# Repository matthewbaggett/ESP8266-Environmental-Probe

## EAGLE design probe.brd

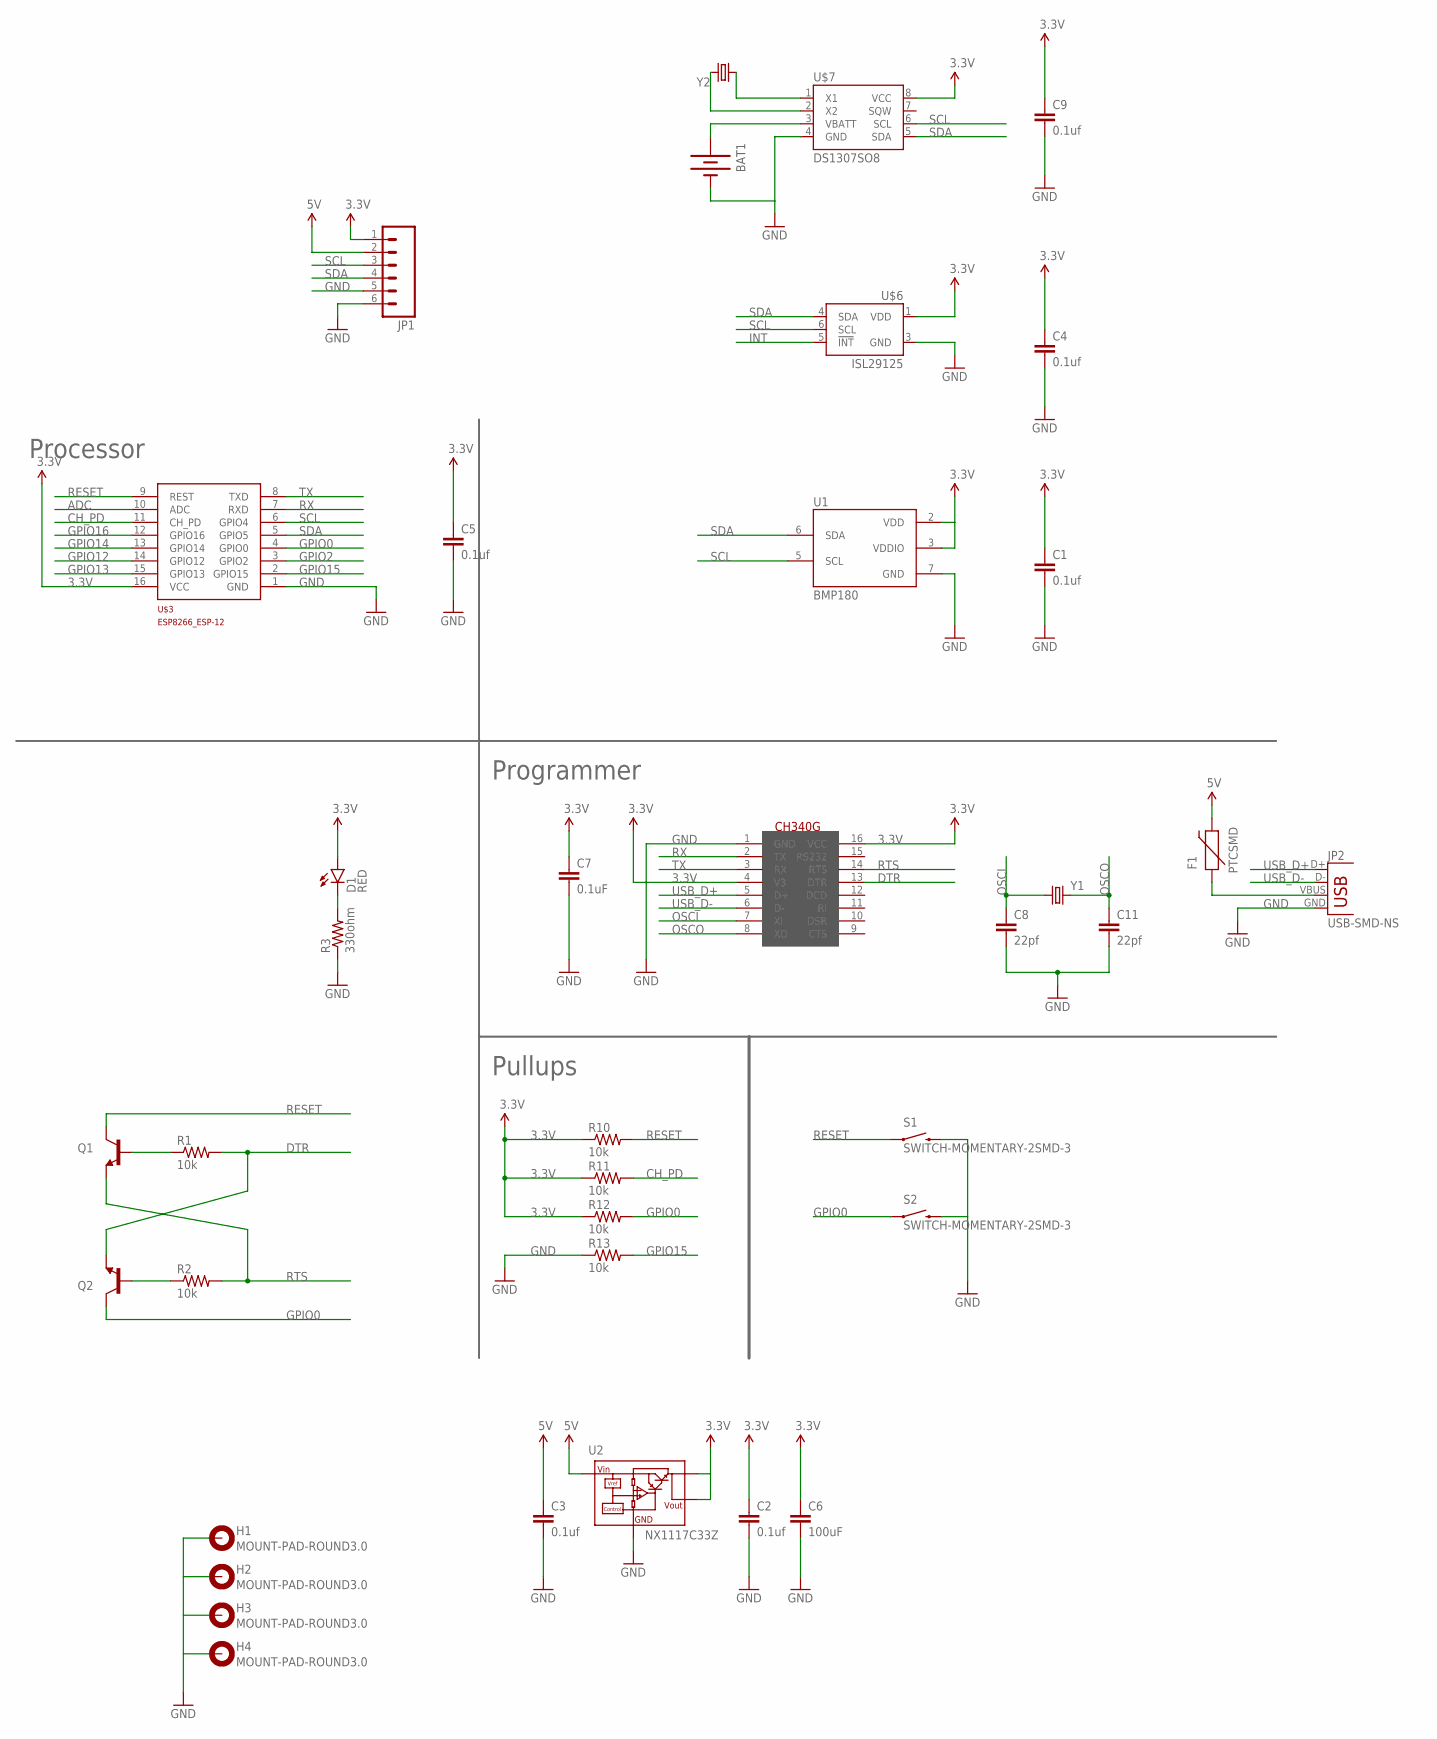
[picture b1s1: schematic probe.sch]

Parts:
BAT1: BATTERY12MM; BATTCON_12MM
C1, C2, C3, C4, C5, C9: 0.1uf; 1206
C6: 100uF; 1210
C7: 0.1uF; 1206
C8, C11: 22pf; 1206
D1: RED; LED-1206
F1: PTCSMD; PTC-1206
H1, H2, H3, H4: MOUNT-PAD-ROUND3.0; 3,0-PAD
JP1: M06SMD-1MM; 1X06-1MM
JP2: USB-SMD-NS; USB-MINIB-NOSTOP
Q1, Q2: TRANSISTOR_NPNSOT23-3; SOT23-3
R1, R2, R10, R11, R12, R13: 10k; 1206
R3: 330ohm; 1206
S1, S2: SWITCH-MOMENTARY-2SMD-3; TACTILE_SWITCH_SMD-3
U1: BMP180
U2: NX1117C33Z; SOT223
U$2: CH340G; SOIC16
U$3: ESP8266_ESP-12; ESP8266-ESP12
U$6: ISL29125; ODFN-LD-6
U$7: DS1307SO8; SO08
Y1: CRYSTALSMD; HC49UP
Y2: CRYSTALTC38H; TC38H

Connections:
3.3V: C1.1, C2.1, C4.1, C5.1, C6.1, C7.1, C9.1, D1.A, JP1.1, R10.1, R11.1, R12.1, U1.2 (VDD), U1.3 (VDDIO), U2.2 (VOUT1), U2.4 (VOUT), U$2.4 (V3), U$2.16 (VCC), U$3.16 (VCC), U$6.1 (VDD), U$7.8 (VCC)
5V: C3.1, F1.2, JP1.2, U2.3 (VIN)
ADC: U$3.10 (ADC)
CH_PD: R11.2, U$3.11 (CH_PD)
DTR: Q2.2 (E), R1.2, U$2.13 (DTR)
GND: BAT1.GND (-), C1.2, C2.2, C3.2, C4.2, C5.2, C6.2, C7.2, C8.2, C9.2, C11.2, H1.B3,0, H2.B3,0, H3.B3,0, H4.B3,0, JP1.5, JP1.6, JP2.GND, R3.1, R13.1, S1.4 (2), S2.4 (2), U1.7 (GND), U2.1 (GND), U$2.1 (GND), U$3.1 (GND), U$6.3 (GND), U$7.4 (GND)
GPIO0: Q2.3 (C), R12.2, S2.1, U$3.4 (GPIO0)
GPIO2: U$3.3 (GPIO2)
GPIO12: U$3.14 (GPIO12)
GPIO13: U$3.15 (GPIO13)
GPIO14: U$3.13 (GPIO14)
GPIO15: R13.2, U$3.2 (GPIO15)
GPIO16: U$3.12 (GPIO16)
INT: U$6.5 (!INT)
unnamed: F1.1, JP2.VBUS
unnamed: Q1.1 (B), R1.1
unnamed: BAT1.PWR@1 (+), U$7.3 (VBATT)
unnamed: U$7.2 (X2), Y2.2
unnamed: Q2.1 (B), R2.1
unnamed: U$7.1 (X1), Y2.1
unnamed: D1.C, R3.2
OSCI: C8.1, U$2.7 (XI), Y1.1
OSCO: C11.1, U$2.8 (XO), Y1.2
RESET: Q1.3 (C), R10.2, S1.1, U$3.9 (REST)
RTS: Q1.2 (E), R2.2, U$2.14 (RTS)
RX: U$2.2 (TX), U$3.7 (RXD)
SCL: JP1.3, U1.5 (SCL), U$3.6 (GPIO4), U$6.6 (SCL), U$7.6 (SCL)
SDA: JP1.4, U1.6 (SDA), U$3.5 (GPIO5), U$6.4 (SDA), U$7.5 (SDA)
TX: U$2.3 (RX), U$3.8 (TXD)
USB_D+: JP2.D+, U$2.5 (D+)
USB_D-: JP2.D-, U$2.6 (D-)

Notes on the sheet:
Programmer
Processor
Pullups

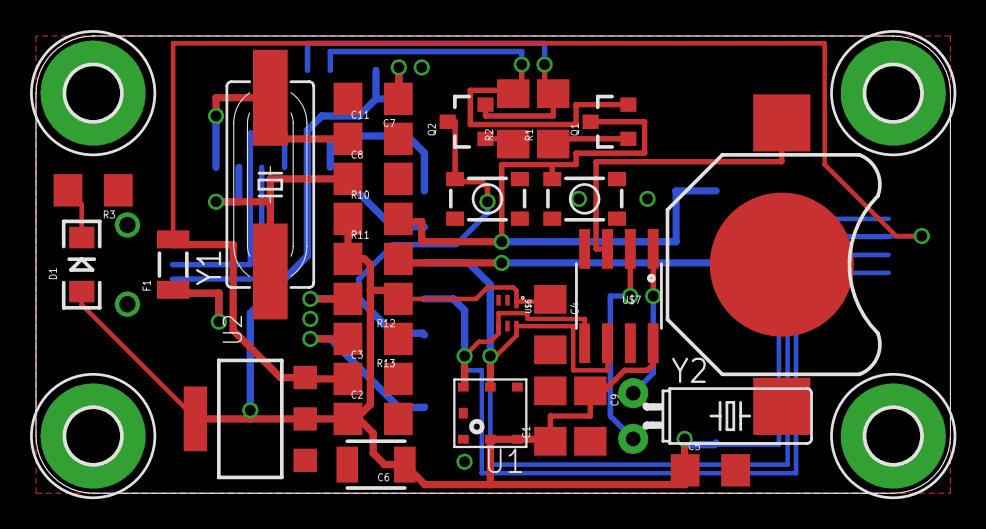
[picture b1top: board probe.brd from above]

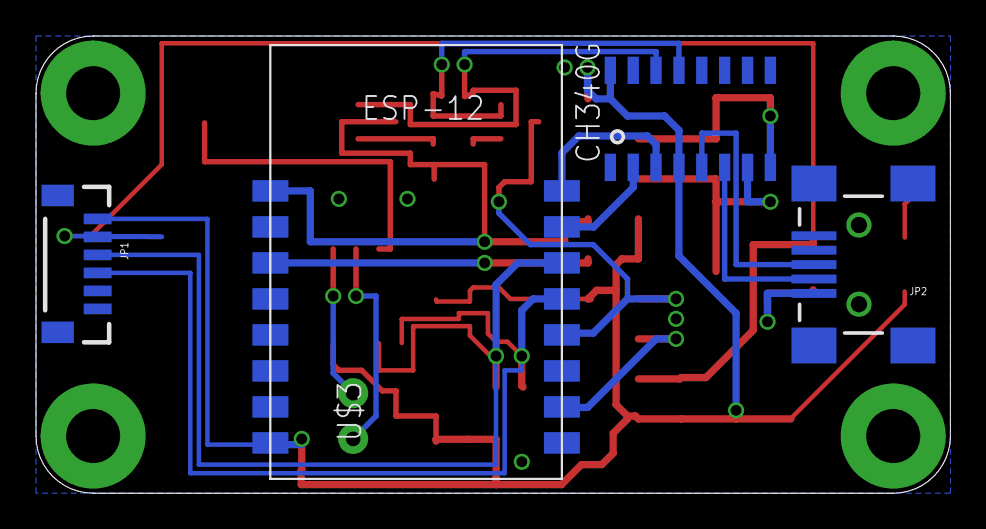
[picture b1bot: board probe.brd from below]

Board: 2 copper layers, 50.8 x 25.4 mm, 38 parts (4 on the bottom side), 24 nets.

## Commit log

2016-06-19 Initial probe board
2016-06-19 Rounded corners
2016-06-19 Adding images of schematic and board

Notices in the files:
parts and their libraries:
SparkFun-Capacitors: Licensing: Creative Commons ShareAlike 4.0 International - https://creativecommons.org/licenses/by-sa/4.0
SparkFun: Licensing: CC v3.0 Share-Alike You are welcome to use this library for commercial purposes.
